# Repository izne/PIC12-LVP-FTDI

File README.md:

# PIC12 Low-voltage programmer board for FT23 adapters
A minimalistic PIC12 low-voltage programmer (ICSP LVP) breakout board for FTDI FT232R adapters

# Purpose
Using an FTDI adapter, one can program a PIC12-series microcontroller using the ICSP LVP method.

# LVP Limitations
Note that ...

# General
The board can be used generally for ICSP LVP programming but a socket is mounted that suits a demonstrator case with PIC12F1840. Using another socket, socket adapter or simply jumper wires would make it possible for a variety of other PIC microcontrollers, that support LVP.

# Board renders

# PICPgm on Windows

# fpicprog on Linux

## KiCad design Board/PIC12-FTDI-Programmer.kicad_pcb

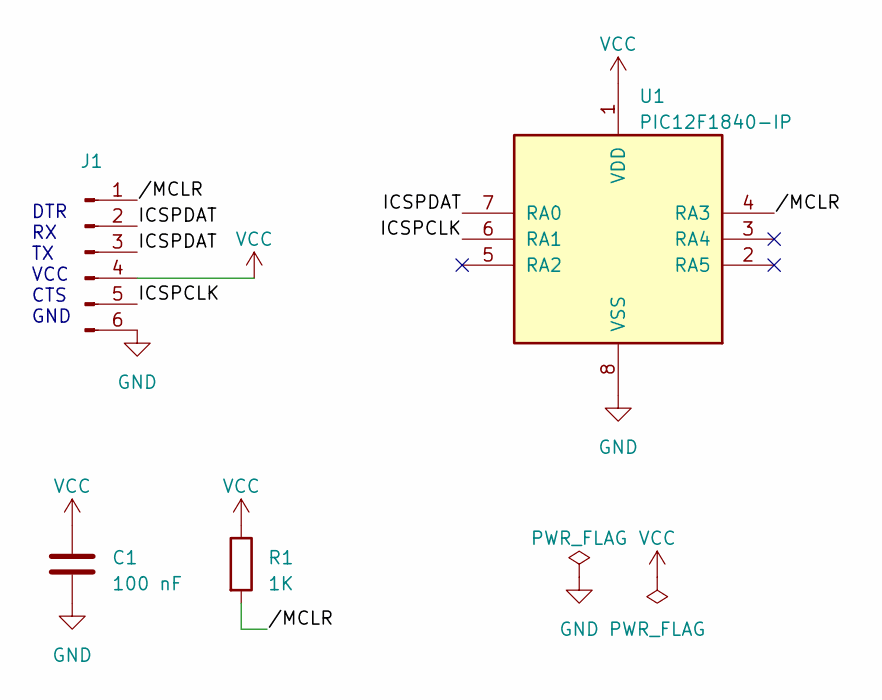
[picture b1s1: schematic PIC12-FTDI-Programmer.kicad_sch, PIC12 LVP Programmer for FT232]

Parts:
C1: 100 nF; C_Disc_D3.4mm_W2.1mm_P2.50mm
J1: Conn_01x06_Pin; PinSocket_1x06_P2.54mm_Vertical
R1: 1K; R_Axial_DIN0204_L3.6mm_D1.6mm_P7.62mm_Horizontal
U1: PIC12F1840-IP; DIP-8_W7.62mm_Socket

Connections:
/ICSPCLK: J1.5, U1.6 (RA1)
/ICSPDAT: J1.2, J1.3, U1.7 (RA0)
//MCLR: J1.1, R1.2, U1.4 (RA3)
GND: C1.2, J1.6, U1.8 (VSS)
VCC: C1.1, J1.4, R1.1, U1.1 (VDD)

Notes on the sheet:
DTR RX TX VCC CTS GND

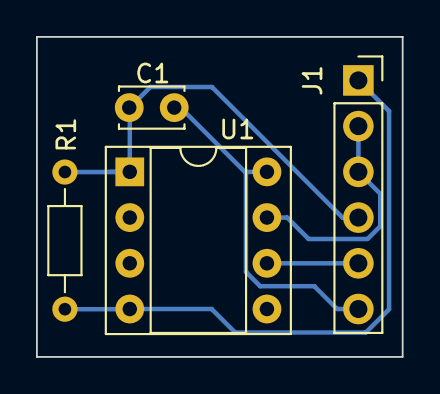
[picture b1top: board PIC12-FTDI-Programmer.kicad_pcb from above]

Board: 2 copper layers, 20.3 x 17.8 mm, 4 parts (0 on the bottom side), 5 nets.

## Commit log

2024-03-29 Initial commit of working filees
2024-03-29 Adding images
